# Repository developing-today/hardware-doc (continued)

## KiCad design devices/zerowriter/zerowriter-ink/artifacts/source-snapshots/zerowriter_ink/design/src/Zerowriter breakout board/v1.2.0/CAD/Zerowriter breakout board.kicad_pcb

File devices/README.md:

# Hardware devices

Each device record links to **every component it contains**; each [component record](../components/README.md) links back to the devices that use it, and to its [vendor sourcing guide](../vendors/README.md).

## Seeed Studio

- [Seeed Studio XIAO ESP32S3 Sense](seeed-studio/xiao-esp32s3-sense/README.md), SKU 113991115, retrieved 2026-08-24 — vendor guide: [Seeed Studio](../vendors/seeed-studio/README.md)

A 17.78 x 21.14 mm ESP32-S3R8 board with a detachable camera / PDM microphone / microSD daughterboard on a 30-pin Hirose board-to-board connector. Notable because Seeed publishes **KiCad sources under CC BY-SA 4.0**, which allowed the otherwise-undocumented [board-to-board connector pinout](seeed-studio/xiao-esp32s3-sense/pinouts-and-buses.md#2-the-j3-board-to-board-connector-sense-daughterboard-interface) to be reconstructed from the PCB netlist.

Three findings from that pass are worth knowing before buying one: the **user LED and the microSD chip-select are the same pin**; the **daughterboard consumes all four JTAG pins**, so hardware debugging is impossible with it attached; and the shipped **factory firmware contains hardcoded Wi-Fi credentials** and cannot connect to your network.

## Waveshare

- [Waveshare ESP32-S3-Knob-Touch-LCD-1.8](waveshare/esp32-s3-knob-touch-lcd-1.8/README.md), product ID 31623, retrieved 2026-08-21 — vendor guide: [Waveshare](../vendors/waveshare/README.md)
- [Waveshare ESP32-S3-ePaper-3.97](waveshare/esp32-s3-epaper-3.97/README.md), SKUs **33552 / 33810 / 33811**, **USD 34.99–47.99**, retrieved 2026-09-01 — the knowledge base's first Waveshare **e-paper** board (all others are LCD). Same SoC, memory, 3.97" 4-grey panel **and SSD1677 controller** as the [M5Stack PaperMono](m5stack/papermono/README.md); active area matches to 0.01 mm and DPI exactly. **It has no expansion header** — which refutes the "prefer a Waveshare board *with expansion*" advice it was written to support. Schematic, panel manual and vendor source retained; [pinouts](waveshare/esp32-s3-epaper-3.97/pinouts-and-buses.md) · [conflicts](waveshare/esp32-s3-epaper-3.97/gaps-and-conflicts.md)

**Waveshare's other ESP32 e-paper boards** — surveyed 2026-09-01, stub records, not researched in depth. Recorded so the population is known:

| Board | Price, 2026-09-01 | Why it is here |
|---|---|---|
| [e-Paper ESP32 Driver Board](waveshare/e-paper-esp32-driver-board/README.md) | USD 14.99 | Original ESP32; drives **23 documented raw panels** over a 24-pin FPC. The oldest and most widely deployed of the family |
| [ESP32-S3-ePaper-1.54](waveshare/esp32-s3-epaper-1.54/README.md) | USD 15.99–22.99 | 1.54" 200 × 200. **Has the 2 × 6 2.54 mm expansion header the 3.97" lacks** — 40 000 pixels instead of 384 000 |
| [ESP32-C6-ePaper-1.54](waveshare/esp32-c6-epaper-1.54/README.md) | USD 16.99–17.99 | Same, on **ESP32-C6 — Wi-Fi 6, Zigbee/Thread**, plus a TCA9554 I/O expander |
| [ESP32-S3-PhotoPainter](waveshare/esp32-s3-photopainter/README.md) | USD 82.99–83.99 | 7.3" Spectra 6 in a wood frame. **An appliance, not a development board** — and the `PhotoPainter` name covers four products, only one of which is ESP32 |

A sibling of this board, the **Guition JC3636K518**, is documented — as far as the evidence allows — in [clones-and-variants.md §5](../guides/markets/clones-and-variants.md#5-worked-example--waveshare-knob-board-and-guition-jc3636k518). It is not a separate device record here because we have not handled one.

### ESP32-P4 round-display boards

Retrieved 2026-08-24. Two variants of **one PCB**, differing only in the fitted round MIPI-DSI panel. Both use the [ESP32-P4](../components/espressif/esp32-p4/README.md) with an ESP32-C6-MINI-1 companion radio over SDIO — the same no-radio-on-the-P4 pattern as Espressif's own boards below.

| Board | Panel | Status | Notes |
|---|---|---|---|
| [ESP32-P4-WIFI6-Touch-LCD-3.4C](waveshare/esp32-p4-wifi6-touch-lcd-3.4c/README.md) | 3.4″ **800 × 800** | on sale, SKU **31523** | Crisper (~333 ppi) |
| [ESP32-P4-WIFI6-Touch-LCD-4C](waveshare/esp32-p4-wifi6-touch-lcd-4c/README.md) | 4″ **720 × 720** | on sale, SKU **31522** | Larger but coarser (~255 ppi) |
| [Shared XC platform record](waveshare/esp32-p4-wifi6-touch-lcd-xc-shared/README.md) | — | — | Schematic, demo archive, pin map, architecture |

`XC` is Waveshare's own family wildcard: both wikis link the **same** schematic and demo archive under an `ESP32-P4-WIFI6-Touch-LCD-XC` path, so those artifacts are stored once. The variants differ in exactly three things — resolution constants, the physical panel, and a single byte in the JD9365 init sequence.

Both are sold under **one listing** at $64.99–$74.99 via a *Version Options* selector — the URL says `3.4c` but serves both. Waveshare maintain an official Apache-2.0 repository, a published BSP component (`waveshare/esp32_p4_wifi6_touch_lcd_xc` 3.0.1) and factory firmware for both: see [official repo and community](waveshare/esp32-p4-wifi6-touch-lcd-3.4c/official-repo-and-community.md).

## Espressif — official ESP32-P4 development boards

Retrieved 2026-08-21. All five are built on the [ESP32-P4](../components/espressif/esp32-p4/README.md), which has **no radio**; each carries a companion Wi-Fi/Bluetooth module. The `P4X` prefix denotes a board fitted with ESP32-P4 chip revision **v3.1 or later** — it is **not** a different chip.

| Board | Status | Companion radio | Distinguishing feature | Sources |
|---|---|---|---|---|
| [ESP32-P4X-Function-EV-Board](espressif/esp32-p4x-function-ev-board/README.md) | current | ESP32-C6-MINI-1 (2.4 GHz Wi-Fi 6) | Flagship multimedia board: 7″ 1024×600 MIPI-DSI touch panel, MIPI-CSI camera, Ethernet, audio, USB HS host + device | [manifest](espressif/esp32-p4x-function-ev-board/sources.md) |
| [ESP32-P4X-C5-Function-EV-Board](espressif/esp32-p4x-c5-function-ev-board/README.md) | current | **ESP32-C5-MINI-1 (2.4 + 5 GHz Wi-Fi 6)** | Same design with **dual-band** Wi-Fi; **the only P4 board whose main-board schematic, PCB layout and dimensions Espressif publishes** | [manifest](espressif/esp32-p4x-c5-function-ev-board/sources.md) |
| [ESP32-P4X-EYE](espressif/esp32-p4x-eye/README.md) | current | ESP32-C6-MINI-1U (external antenna) | Enclosed hand-held **camera**: 2 MP MIPI-CSI, 1.54″ SPI LCD, rotary encoder, battery, on-device YOLOv11-nano demo | [manifest](espressif/esp32-p4x-eye/sources.md) |
| [ESP32-P4-Function-EV-Board](espressif/esp32-p4-function-ev-board/README.md) | **EOL** | ESP32-C6-MINI-1 | Predecessor of the P4X board; **retains the published schematic / PCB / dimensions / assembly set** | [manifest](espressif/esp32-p4-function-ev-board/sources.md) |
| [ESP32-P4-EYE](espressif/esp32-p4-eye/README.md) | **EOL** | ESP32-C6-MINI-1U | Predecessor of the P4X-EYE; **retains the published schematic and PCB layout** | [manifest](espressif/esp32-p4-eye/sources.md) |

⚠ **Both EOL user guides moved between 2026-08-21 and 2026-08-28** — Espressif dropped the `eol/`
path segment, the originally-cited URLs now return HTTP 404, and neither has an Internet Archive
capture. Current URLs and the full finding are in
[the EOL board's manifest §4](espressif/esp32-p4-function-ev-board/sources.md#4-retrieval-findings).

There is **no ESP32-P4 Korvo board.** The Korvo line is an audio/HMI family built on the ESP32-S3 (`ESP32-S3-Korvo-2`, `ESP32-S3-Korvo-2-LCD`) and the newer S3.1 (`ESP32-S31-Korvo-1`). See [ESP32-P4 §1](../components/espressif/esp32-p4/README.md#1-identity-and-variants) and the board records above.

Documents Espressif publishes once and links from several of these boards are stored in [`espressif/shared-artifacts/`](espressif/shared-artifacts/README.md) rather than duplicated into each board.

The companion-radio arrangement these five boards share — and how it contrasts with the ESP32-S3 + ESP32-U4WDH retrofit on the Waveshare knob board — is mapped in [ecosystem-and-product-lines.md §6](../guides/espressif/ecosystem-and-product-lines.md#6-the-companion-radio-pattern-p4--c6c5).

## Soldered Electronics

Retrieved 2026-08-24. Osijek, Croatia — makers of the **Inkplate** e-paper series. Vendor guide: [Soldered Electronics](../vendors/soldered-electronics/README.md).

| Board | Panel | Hardware rev | Arduino target | Sources |
|---|---|---|---|---|
| [Inkplate 5](soldered-electronics/inkplate-5/README.md) | 5.2″ **960 × 540** | V1.2.0 | `Inkplate5` | [manifest](soldered-electronics/inkplate-5/sources.md) |
| [Inkplate 5 Gen 2](soldered-electronics/inkplate-5-gen2/README.md) | 5.2″ **1280 × 720** | V1.1.0 | `Inkplate5V2` | [manifest](soldered-electronics/inkplate-5-gen2/sources.md) |

Both generations share **one full technical record** — [`inkplate-5/README.md`](soldered-electronics/inkplate-5/README.md) — because they differ in **exactly one component**, the panel. Everything else (ESP32-WROVER, TPS65186 PMIC, PCAL6416A expander, PCF85063A RTC) is common. The Gen 2 keeps its own page because Soldered publish its hardware design in a **separate upstream repository**.

Worth knowing before integrating one: Soldered ship **CE and UKCA compliance documents and multilingual safety sheets inside the public hardware repository**, which is unusually thorough for an open-hardware vendor. Hardware is **TAPR OHL**; the Arduino library is **LGPL-3.0**.

## ZeroWriter

Open-source e-paper typewriters by Adam Wilk. Vendor guide: [Zerowriter](../vendors/zerowriter/README.md).

| Device | Status | Platform | Retrieved |
|---|---|---|---|
| [ZeroWriter Ink](zerowriter/zerowriter-ink/README.md) | shipping since Jan 2026; Crowd Supply, funded 2024-10-17, $285 | Respun [Inkplate 5 Gen 2](soldered-electronics/inkplate-5-gen2/README.md) + a second ESP32 for the keyboard | 2026-08-24 |
| [Zerowriter Fold](zerowriter/zerowriter-fold/README.md) | **unshipped** — Kickstarter live at snapshot, ~$239 First Wave / ~$329 retail, ships late 2026 | Claimed **in-house** hardware; 6″ **frontlit** e-ink, folding laptop-style case, hot-swap Choc keyboard | 2026-08-24 |

**ZeroWriter Ink** was built **in collaboration with Soldered Electronics**. The headline finding is that the device contains **two ESP32s** — an ESP32-WROVER on the display board and an ESP32-WROOM-32U-N4 on the keyboard PCB — which is stated nowhere in the campaign material and was recovered only from the project's own KiCad BOMs.

Its main board is a **respin of the [Inkplate 5 Gen 2](soldered-electronics/inkplate-5-gen2/README.md)**, not the stock product: 8 parts added, 14 removed, 20 values changed, including a swap from a linear to a switch-mode charger. Firmware written against the Inkplate Arduino library should run, but **power, charging, USB and SD paths differ** — see [the BOM comparison](zerowriter/zerowriter-ink/README.md).

Its Raspberry-Pi predecessor, **ZeroWriter 1**, silently patched two files in Waveshare's vendored e-paper driver library; both changes are analysed in [zerowriter1-epaper-driver-notes.md](zerowriter/zerowriter-ink/zerowriter1-epaper-driver-notes.md).

**Zerowriter Fold** is documented **from vendor marketing material only** — the Kickstarter campaign page bot-blocks every user agent tried and was never read. No design files, teardown, review or unit exists. Treat every figure as a vendor claim about an unshipped product; the record's [source manifest](zerowriter/zerowriter-fold/sources.md) states exactly what that evidence can and cannot support. The consequential claim is that the Fold uses **in-house hardware** rather than an Inkplate — if accurate, none of the Inkplate research transfers to it.

## M5Stack

Retrieved **2026-09-01**. Two SKUs of **one board**, launched together on 2026-08-21 and both out of stock nine minutes later.

| Board | SKU | Price | Distinguishing feature | Sources |
|---|---|---|---|---|
| [PaperMono](m5stack/papermono/README.md) | **C153** · FCC **`2AN3WM5PAPERMONO`** | USD 65.00 | Grey case, **NFC (ST25R3916) + LoRa (Stamp LoRa-1262)** | [**certification**](m5stack/papermono/certification.md) · [sources](m5stack/papermono/sources.md) · [research log](m5stack/papermono/research-log.md) · [commands](m5stack/papermono/commands.md) |
| [PaperMono-Lite](m5stack/papermono-lite/README.md) | **C153-Lite** / `C153-LITE` | USD 55.00 | White case, **no NFC, no LoRa**; 72.4 g vs 74.7 g. Everything else identical, battery included | shares the PaperMono's manifests |

> **Certification, 2026-09-20.** The PaperMono record previously said in seven
> places that no certification of any kind existed for this board. **It is
> certified** — FCC ID **`2AN3WM5PAPERMONO`**, two grants issued 2026-08-12 — and
> M5Stack simply publishes nothing about it. The filing's eleven exhibits have
> been mined into [`certification.md`](m5stack/papermono/certification.md):
> certified bands and conducted power per mode, the antenna's measured gain
> (**−5 dBi** at 910 MHz, 15.9 % efficient), SAR at **0 mm on all six faces**,
> and **the only public PCB photographs of this board**. Two things a builder
> needs: **US LoRa is 903.0–914.9 MHz only**, and **Wi-Fi and BLE cannot transmit
> simultaneously**. M5Stack also filed its **full architecture diagram as the FCC
> label**, which is a second primary source for the pin map.

A 3.97″ 480 × 800 frontlit touch e-paper handheld on an ESP32-S3R8. Best understood as **a battery-first low-power platform that happens to have a display**, not an e-paper board that happens to have a battery: it has five hardware power states and can wake on RTC alarm, motion, touch or keys **with the application processor unpowered**. The full record: [`papermono/`](m5stack/papermono/README.md), with [pinouts and buses](m5stack/papermono/pinouts-and-buses.md), [power architecture](m5stack/papermono/power-architecture.md) and [gaps and conflicts](m5stack/papermono/gaps-and-conflicts.md).

Four things to know before buying or building for one:

- **There is no expansion connector at all** — no Grove, no M-Bus. Every GPIO is committed; the only way in is the shared I²C bus. This is unusual for an M5Stack core and is the single biggest constraint.
- **Two auxiliary microcontrollers sit between the application processor and most of the board.** Panel power and reset, touch power and reset, microSD power and detect, microphone power, NFC enable, LoRa reset, two of three LED colours and the charger's bus gate are all behind the **M5IOE1** expander; reset, boot mode, rail enables and every wake source are behind the **M5PM1** power manager. Neither is optional, and both are the *same* Puya PY32L020F15U6 die running different M5Stack firmware.
- **`PYG3` denotes two different pins**, one on each of those chips — the frontlight PWM and the e-paper rail enable. Getting it wrong silently kills the display. [The whole hazard, and how it was resolved from the schematic](m5stack/papermono/pin-naming-and-the-pyg-ambiguity.md).
- **Do not read PaperMono as a successor to the M5PaperS3.** Against the PaperS3 it has ~35 % fewer pixels, 4 grey levels instead of 16, a smaller battery and no expansion port, while adding a frontlight, NFC, LoRa and the power architecture. A repositioning, not an upgrade.

⚠ **Nothing in either record was verified on physical hardware.** Every behavioural claim is `inferred`, `reported-working` or read from vendor source. The board sold out within minutes of launch and had not restocked eleven days later, so no unit could be obtained — and for the same reason there were, at the snapshot date, **zero written reviews and one hands-on video** anywhere. The real independent evidence is four third-party GitHub projects, two with credible hardware validation.

M5Stack publishes a complete schematic and datasheets for both of its custom chips, which is better hardware disclosure than most comparable vendors — but **no C153 directory exists in `m5stack/M5_Hardware`**, so there is no machine-readable netlist and the pin map was recovered by parsing invisible Altium marker text out of the published PDF. Method and limitations: [`commands.md`](m5stack/papermono/commands.md#altium-pdf-tooling).

### DinMeter — *added 2026-09-04*

A 1/32-DIN panel instrument built on a Stamp module: orange rotary encoder, 1.14" display, buzzer and a **6–36 V DC input**, in a DIN 43700 cutout. M5Stack publishes a **byte-identical** schematic and STL for both revisions, so the v1.1 record is scoped to the module substitution that is the entire content of the revision.

| Device | SKU | Record | Notes |
|---|---|---|---|
| **DinMeter** | `K134` | [`m5stack/dinmeter`](m5stack/dinmeter/README.md) | 1/32-DIN panel instrument: orange rotary encoder, 1.14" ST7789V2 135×240, BM8563 RTC, buzzer, **6–36 V DC input**, Li-ion charger + latch, PORT.A/B. Stamp-S3 core module. **`[EOL]` at the vendor, 2026-09-04** |
| **DinMeter v1.1** | `K134-V11` | [`m5stack/dinmeter-v1.1`](m5stack/dinmeter-v1.1/README.md) | Same carrier with a **Stamp-S3A** module and an ST7789P3 display. Scoped revision record — M5Stack publishes a **byte-identical** schematic and STL for both. Includes [`stamp-s3-to-s3a-delta.md`](m5stack/dinmeter-v1.1/stamp-s3-to-s3a-delta.md), the full schematic-derived module delta |

### Cardputer family — *added 2026-09-04*

Card-sized computers with a 56-key QWERTY keyboard over a 1.14″ 240×135 display. Five records; the ADV is the full-depth one. Note that **the v1.0 and v1.1 share one published schematic file byte-for-byte** (SHA-256 `6016c1fe…`), so the revision is a module substitution — Stamp-S3 → Stamp-S3A — with an undocumented or unchanged mainboard, and the document alone cannot say which.

| Device | Manufacturer | SKU | SoC | Notes |
|---|---|---|---|---|
| [Cardputer ADV](m5stack/cardputer-adv/README.md) | M5Stack | `K132-Adv` | ESP32-S3FN8 | Card-sized computer, 56-key TCA8418 keyboard, ES8311 audio, BMI270, 14-pin CAP expansion header. **Full-depth record.** |
| [Cardputer v1.1](m5stack/cardputer-v1.1/README.md) | M5Stack | `K132-V11` | ESP32-S3FN8 | Stamp-S3A refresh of the original; 74HC138 keyboard. **`[EOL]` at 2026-09-04.** |
| [Cardputer v1.0](m5stack/cardputer-v1.0/README.md) | M5Stack | `K132` | ESP32-S3FN8 | The original; StampS3 module. Shares a published schematic file with v1.1. |
| [Cardputer Mesh Kit](m5stack/cardputer-mesh-kit/README.md) | M5Stack | `K152` | ESP32-S3FN8 | Cardputer ADV + Cap LoRa-1262 bundle; officially licensed Meshtastic device. |
| [CardputerZero](m5stack/cardputer-zero/README.md) | M5Stack | `C154` / `C155` | **Raspberry Pi CM0** | Linux handheld in the Cardputer form factor. Vendor marks it *work in progress*. |

⚠ **The Cardputer ADV and the CardputerZero are not comparable devices** despite sharing a name, a form factor, a keypad scanner and an expansion connector: one is a microcontroller, the other a Linux computer, and their EXT headers are **not pin-compatible** — the Zero's left column is USB/GPIO/SPI0 and its UART pair is reversed relative to the ADV's.

### Cardputer expansions — LoRa, sub-GHz and NFC — *added 2026-09-04*

Nine records covering M5Stack's radio expansions for the Cardputer line, from the Grove-attached E220 units of 2023 to the **Cap CC1101 & NFC** released 2026-08-28. Entry point: [`m5stack/cap-lora-1262/`](m5stack/cap-lora-1262/README.md); the two portability-focused guides are [`features/lora.md`](m5stack/cap-lora-1262/features/lora.md) and [`features/nfc.md`](m5stack/cap-cc1101/features/nfc.md), both written for someone adding these capabilities to *other* firmware.

| Device | Notes | Depth |
|---|---|---|
| [M5Stack Cap LoRa-1262 (U214)](m5stack/cap-lora-1262/README.md) | Cardputer-Adv expansion — SX1262 LoRa + ATGM336H-6N GNSS, 868–923 MHz, Meshtastic-supported upstream | full |
| [M5Stack Cap CC1101 & NFC (U219)](m5stack/cap-cc1101/README.md) | Cardputer-Adv expansion — CC1101 sub-GHz (315/433/868/915 MHz, dual SP3T switched) + ST25R3916 NFC over SPI | full |
| [M5Stack Cap LoRa868 (U201)](m5stack/cap-lora868/README.md) | The **first** Cardputer-Adv LoRa expansion, 2025-09-05, now EOL — predecessor of the Cap LoRa-1262 | medium |
| [M5Stack Cardputer Mesh Kit (K152)](m5stack/cardputer-mesh-kit/README.md) | Bundle: Cardputer-Adv + Cap LoRa-1262, pre-flashed Meshtastic, the only Meshtastic-registration-eligible configuration | medium |
| [M5Stack LoRa Unit (E220)](m5stack/unit-lora-e220/README.md) | Grove/UART LLCC68 modem — attaches to *any* Cardputer, but **not** a Meshtastic path | light |
| [M5Stack LoRaWAN Unit (STM32WLE5)](m5stack/unit-lorawan-stm32wle5/README.md) | Grove/UART LoRaWAN modem, **region per SKU**, RAK3172 module | light |
| [M5Stack Unit C6L (U202)](m5stack/unit-c6l/README.md) | Self-contained ESP32-C6 + SX1262 Meshtastic node on a Grove cable — the route for an **original** Cardputer | light |
| [M5Stack Stamp C6LoRa (S012)](m5stack/stamp-c6lora/README.md) | Solder-down ESP32-C6 + SX1262 SMD module — **not** a Cardputer expansion | light |

⚠ **Initialising the Cap LoRa-1262 requires one non-obvious step**: M5Stack states that the RF antenna switch must be enabled by setting **`P0` of the Cap's PI4IOE I/O expander HIGH**, over the host's *internal* I²C bus. Omit it and the radio transmits into a disconnected antenna.

## Xteink (阅星瞳 / 星瞳 "Star Pupil")

Shenzhen maker of low-cost pocket e-ink readers, and the hardware target of the
CrossPoint Reader / FreeInk firmware ecosystem. **Six products**, four of them
ESP32-based. See the [family index](xteink/README.md).

| Device | SoC | Panel | Price (2026-09-04) | Record |
|---|---|---|---|---|
| [X4 Pro](xteink/x4-pro/README.md) | ESP32-S3, 8 MB PSRAM | 4.26″ 800×480, GT911 touch, warm/cool frontlight | **$99** | deep |
| [X4](xteink/x4/README.md) | ESP32-C3 | 4.26″ 800×480 | **delisted** | deep |
| [X3](xteink/x3/README.md) | ESP32-C3 | 3.7″ 792×528, ~257 PPI, IMU + NFC | **$69** | deep |
| [X4 Classic](xteink/x4-classic/README.md) | ESP32-S3, 8 MB PSRAM | 4.26″ 800×480, 7 buttons, IMU | not listed | medium |
| [S4](xteink/s4/README.md) | **Android 11** | not established | ¥339 (China) | stub |
| [Nano / Tong Card 瞳卡](xteink/nano/README.md) | **none — passive NFC-powered** | four-colour e-paper card | not captured | stub |

**Note the naming trap:** the X4 Pro is *not* an enhanced X4. They share a screen
size and a brand; different SoC architecture, flash layout, input hardware and
charging connector. Firmware for one will not run on the other.

Three axes of variation are **invisible from outside** and none is externally marked: the **panel controller** (the X3 ships a UC8253 *or* a UC8279d; the X4 family an SSD1677 *or* UC8179 *or* UC8279 — firmware probes the display bus at boot, **except on the X4 Classic, which has no MISO and must trust an NVS byte the factory wrote once**); the **power latch** (at least one X4 revision does not self-latch); and the **USB-lock state**, which owners find **does not correlate with sales channel**.

### Round-two corrections — *2026-09-11*

⚠ **Two rows in the table above are now wrong, and one device is missing from it.** Per this
repository's append-only rule the stale rows are **left exactly as written**; the corrections are
here. The family index [`xteink/README.md`](xteink/README.md) carries the full corrected table.

**1. The X4 Classic launched on 2026-09-06, and it replaced the X4.**
The row above says *"not listed"*. It is listed, and the X4 row's price is the one that is now
historical:

| Device | Marketed as | Listed | Price | Status 2026-09-11 |
|---|---|---|---|---|
| [X4 Classic](xteink/x4-classic/README.md) | **"XTEINK X4 Classic (X4 V2)"** | **2026-09-06** | **USD 79** bare / 95 with base | on sale, in stock |
| [X4](xteink/x4/README.md) | — | — | last observed ~USD 69 | **withdrawn — the product record *and all four of its dedicated accessories* are gone from the catalogue** |

**The vendor's own store title asserts the succession**: the Classic *is* the second version of
the X4. The FCC record agrees — `2BTR9-XTEINKX4` granted 2026-01-05, then `2BTR9-X4C` granted
2026-07-20. On 2026-09-04 the X4's four accessories were still listed but sold out; a week later
the product records themselves had been removed. **That is a completed withdrawal, not a
stockout.**

**2. There is a sixth device, and the vendor has never mentioned it.**

| Device | SoC | Panel | Price | Record |
|---|---|---|---|---|
| [X4 Light](xteink/x4-light/README.md) | **unknown** | **unknown** | **never listed** | certification-only |

**FCC `2BTR9-X4L`, granted 2026-08-13.** No announcement, no store listing, no price, no review,
no community mention. It was found by **enumerating Xteink's FCC grantee code `2BTR9`**, not by
searching for a product name — a vendor's grantee index lists every device it has certified for
the US, including ones it has never announced. Its internal photographs unlock **2027-02-09**;
its external photographs are already public and held in the record. ⚠ **"Light" is a marketing
word and the filing does not define it** — do not infer a specification or a price slot from the
name.

That makes the table above **seven entries**, not six. Four are confirmed ESP32-based; the X4
Light's SoC is **unknown**, and the Nano is a passive NFC card rather than a reader.

**3. ⚠ The certification finding for this family is reversed.** Records in this tree stated that
no FCC or CE filing existed for any Xteink device. **Refuted.** Xteink holds **five granted
Original Equipment authorisations** under grantee code `2BTR9` — X3, X4, X4 Pro, X4 Classic and
X4 Light. The original finding confused *"no mark visible in a product photo"* with *"no grant"*.
Per-device detail and the positive/negative controls that make it evidence:
`xteink/<record>/certification-and-compliance.md`. Corrections are appended beneath every stale
claim and listed in
[`research/passes/index-merge/corrections-requiring-review.md`](../research/passes/index-merge/corrections-requiring-review.md).

One consequence worth surfacing at index level: the `2BTR9-XTEINKX4` filing's **Internal Photos
were never withheld**, which makes them the **first public teardown of the Xteink X4** —
[`xteink/x4/artifacts/certification/`](xteink/x4/artifacts/certification/README.md). The X3's are
public too; the X4 Pro's unlock **2026-12-12**. Schematics are withheld **permanently** on all
five filings, so the FCC is not a route to an Xteink schematic.

## LilyGO (Shenzhen Xin Yuan Electronic Technology; also trades as TTGO)

Vendor guide: [LilyGO / TTGO](../vendors/lilygo/README.md). The **T-Display-S3 family** is a *name*, not a platform: eleven boards, eight display
controllers and four different chargers ship under it. Start at the shared platform record.

| Device | Identity | Depth |
|---|---|---|
| [T-Display-S3 family — shared platform](lilygo/t-display-s3-shared/README.md) | family hub: enumeration evidence, shared artifacts, family-wide traps, [board-revision drift](lilygo/t-display-s3-shared/board-revision-drift.md) | — |
| [T-Display-S3](lilygo/t-display-s3/README.md) | ESP32-S3R8 + 1.9″ 170×320 ST7789V on an **8-bit Intel-8080 parallel** bus. USD 9.04 | **full** |
| [T-Display-S3 Touch](lilygo/t-display-s3-touch/README.md) | same PCB; panel swapped for one with a bonded CST816S → later CST328 | medium |
| [T-Display-S3 AMOLED](lilygo/t-display-s3-amoled/README.md) | 1.91″ 240×536 RM67162 on QSPI; **V1.0 and V2.0 sold concurrently** | full-ish |
| [T-Display-S3 AMOLED Plus](lilygo/t-display-s3-amoled-plus/README.md) | same panel, BQ25896 PMIC + PCF85063ATL RTC + microSD | medium |
| [T-Display-S3 AMOLED 1.64″](lilygo/t-display-s3-amoled-1-64/README.md) | 280×456 CO5300/ICNA3311 + FT3168 + SY6970 | medium |
| [T-Display-S3 AMOLED 1.43″/1.75″](lilygo/t-display-s3-amoled-1-43-1-75/README.md) | round 466×466; **two display and two touch controllers behind one product page** | medium |
| [T4-S3](lilygo/t4-s3/README.md) | the "2.41″ AMOLED": 450×600 RM690B0 + CST226SE. Sold as *T4-S3*, not T-Display-S3 | medium |
| [T-Display AMOLED Lite](lilygo/t-display-amoled-lite/README.md) | 1.47″ 194×368 SH8501B behind a **1.8 V level shifter**; AXP2101 PMU | medium |
| [T-Display-S3 Long](lilygo/t-display-s3-long/README.md) | 3.4″ 180×640 bar; **AXS15231B drives display *and* touch from one die** | full-ish |
| [T-Display-S3 Pro](lilygo/t-display-s3-pro/README.md) | 2.33″ 222×480 ST7796 on plain SPI, camera, microSD, 3 buttons, SY6970 | full-ish |
| [T-Display-S3 Pro MVSRBoard](lilygo/t-display-s3-pro-mvsrboard/README.md) | audio/RTC/haptic backplate for the Pro | stub |
| [T-Display (TTGO, ESP32)](lilygo/t-display-ttgo/README.md) | the ancestor. 1.14″ 135×240 SPI. **The only one WLED supports** | lineage stub |
| [T-QT](lilygo/t-qt/README.md) | thumbnail-sized 128×128 cousin | lineage stub |
| [T-Dongle-S3](lilygo/t-dongle-s3/README.md) | USB-A dongle, 0.96″ ST7735, on-board microSD | lineage stub |
| [T-Display K230 / Kit](lilygo/t-display-k230/README.md) | **the repository's first RISC-V device** — see below | full |

### T-Display K230 — *added 2026-09-04*

- [`lilygo/t-display-k230`](lilygo/t-display-k230/README.md) — **T-Display K230** (SKU `K256`/`-A`/`-B`/`-C`) and **T-Display K230 Kit** (`K256-03`, `K277`, `K256-04`, `K256-04-A`). A 4.1″ AMOLED handheld running **Linux on a 64-bit RISC-V** Kendryte K230, with LoRa, a 2 MP MIPI camera, USB Ethernet, a 40-pin header, and an optional QWERTY keyboard base carrying an nRF9151 LTE-M/GNSS modem. **The repository's first RISC-V device.**

⚠ **LilyGO stock codes collide with chip names.** `K230` is a LilyGO SKU for the transparent-case variant of the **T-Embed CC1101**, an ESP32-S3 board with no Kendryte silicon in it. The Kendryte K230 board's SKUs are `K256*` and `K277`. **Never infer silicon from a LilyGO SKU** — and see the [vendor guide](../vendors/lilygo/README.md) for why the wiki must be verified against the board's GitHub repository.

---

## Nicolai Electronics

- [Nicolai Electronics Tanmatsu](nicolai-electronics/tanmatsu/README.md), retrieved 2026-08-24, hardware repo commit `640805dd` — "the terminal for hackers": an **ESP32-P4** handheld with a QWERTY keyboard, LoRa, a MIPI-DSI display and a 36-pin expansion port, derived from the Dutch hacker-camp badge lineage ([Badge.team](https://badge.team), MCH2022 / WHY2025) but sold as a product.

Notable for **openness rather than volume**: the full KiCad design is published under **CERN-OHL-P** and the firmware under **MIT**, with a git-maintained Sphinx documentation site. The limiting factor on information is that the device is new and low-volume, and the detail is spread across ~10 repositories.

> *Indexed 2026-09-07.* This record was written in the 2026-08-24 pass but was never linked from this index — an orphan found by the cross-link audit at the end of the 2026-09-04/07 sweep. The entry above is a discoverability fix written from the record's own opening section; **the record itself was not reviewed or modified**, and it remains the authority on its own contents.

---

## Flipper Devices

- [Flipper Devices Flipper Zero](flipper-devices/flipper-zero/README.md) — ⚠ **artifact-preservation stub, not a researched device record.** *Added 2026-09-20.*

Created solely to give six **Flipper Devices Inc.** schematic sheets (iButton, NFC, Power, Power and vibro, RFID, Sub-1 GHz CC1101) and seven teardown photographs a correctly-classified home. They were vendored as prior art into [`badgeteam/konsool-zero`](nicolai-electronics/tanmatsu/expansion-boards.md) — a Tanmatsu add-on — and a SHA-256 sweep confirmed they existed in exactly one place, inside a scratch clone.

**No product, pricing, firmware, community or component research has been done.** The sections a full device record requires are *absent, not empty*. What the sheets were mined for is narrow and stated in the record: they establish that konsool-zero copied the Flipper's sub-GHz and 125 kHz analog chains almost part-for-part, changing only the CC1101 reference (26 MHz crystal → 27 MHz oscillator) and the MCU (STM32WB55 → CH32V003F4U6) — which is also how a fabricated "STM32WB55CC on konsool-zero" claim got into this repository and was later refuted.

If you research the Flipper Zero properly, start from those artifacts and replace the stub.

---

## Two new per-record file types — *added 2026-09-11*

Round two of the 2026-09-04 sweep added two kinds of page to device records across the tree.
Neither is listed per-device above; both are worth knowing exist.

| File | What it is | Where |
|---|---|---|
| `certification-and-compliance.md` | Regulatory grants by jurisdiction — FCC ID, grant date, frequencies, test firm, withheld exhibits and embargo dates — **each carrying the positive and negative controls that make an absence finding mean anything**. Method: [`guides/research/finding-certification-records.md`](../guides/research/finding-certification-records.md) | **32 records**: M5Stack, LilyGO and all five Xteink |
| `schematic-netlist.md` | A net list **recovered from the vendor's schematic PDF**, not from EDA sources — connector pinouts, per-net membership and the unrouted or mislabelled nets the trace exposed. Method: [`guides/reverse-engineering/tracing-nets-from-schematic-pdfs.md`](../guides/reverse-engineering/tracing-nets-from-schematic-pdfs.md) | [`lilygo/t-display-s3-shared`](lilygo/t-display-s3-shared/schematic-netlist.md) · [`m5stack/cardputer-adv`](m5stack/cardputer-adv/schematic-netlist.md) · [`m5stack/dinmeter`](m5stack/dinmeter/schematic-netlist.md) · [`m5stack/cap-lora-1262`](m5stack/cap-lora-1262/schematic-netlist.md) · [`m5stack/cap-cc1101`](m5stack/cap-cc1101/schematic-netlist.md) |

Two of those boards also gained a `driver-vs-document-audit.md` — the vendor driver read
side-by-side against the schematic and the datasheet:
[`cardputer-adv`](m5stack/cardputer-adv/driver-vs-document-audit.md) (`M5Cardputer` @ `f1392858`)
and [`dinmeter`](m5stack/dinmeter/driver-vs-document-audit.md) (`M5DinMeter` @ `8ccbad7`).

**Why the tracing worked, and when it will not.** Altium exports embed invisible `CO` / `PI` /
`NL` marker tokens at item coordinates — component outlines, pins and net labels — so a net can
be reconstructed by geometry from the PDF text layer alone. **291 schematic PDFs in this
repository were assessed**; the per-file verdict is in
[`guides/reverse-engineering/schematic-pdf-traceability-census.md`](../guides/reverse-engineering/schematic-pdf-traceability-census.md).
Two traps that census found, both worth checking before concluding a design is undocumented:

- ⚠ **KiCad and EAGLE exports frequently outline their text to vector paths.** `pdftotext` then
  yields **zero words** and the file is permanently untraceable. For
  [`zerowriter/zerowriter-ink`](zerowriter/zerowriter-ink/README.md) and
  [`seeed-studio/xiao-esp32s3-sense`](seeed-studio/xiao-esp32s3-sense/README.md) **a second,
  usable export of the same design sits in the same directory** — prefer the `Eeschema` copies.
- ⚠ **Non-Altium exports carry no `CO`/`PI`/`NL` tokens**, so every binding must be geometric.
  That applies to the Espressif ESP32-P4 board schematics, which are otherwise traceable.

The richest untraced sheet in the repository is the **M5Stack PaperMono**'s
`PaperMono_SCH_V0.6.2` — 6 pages, 144 net-label tokens, fully traceable, and **not traced**,
because that record was owned by another session throughout both rounds.

---

## Related

- [Components](../components/README.md) — the parts these boards are built from
- [Vendor sourcing guides](../vendors/README.md) — [Espressif](../vendors/espressif/README.md) · [Waveshare](../vendors/waveshare/README.md)
- [Espressif ecosystem map](../guides/espressif/ecosystem-and-product-lines.md) · [Marketplace comparison](../guides/markets/vendor-comparison.md) · [Clones and variants](../guides/markets/clones-and-variants.md)

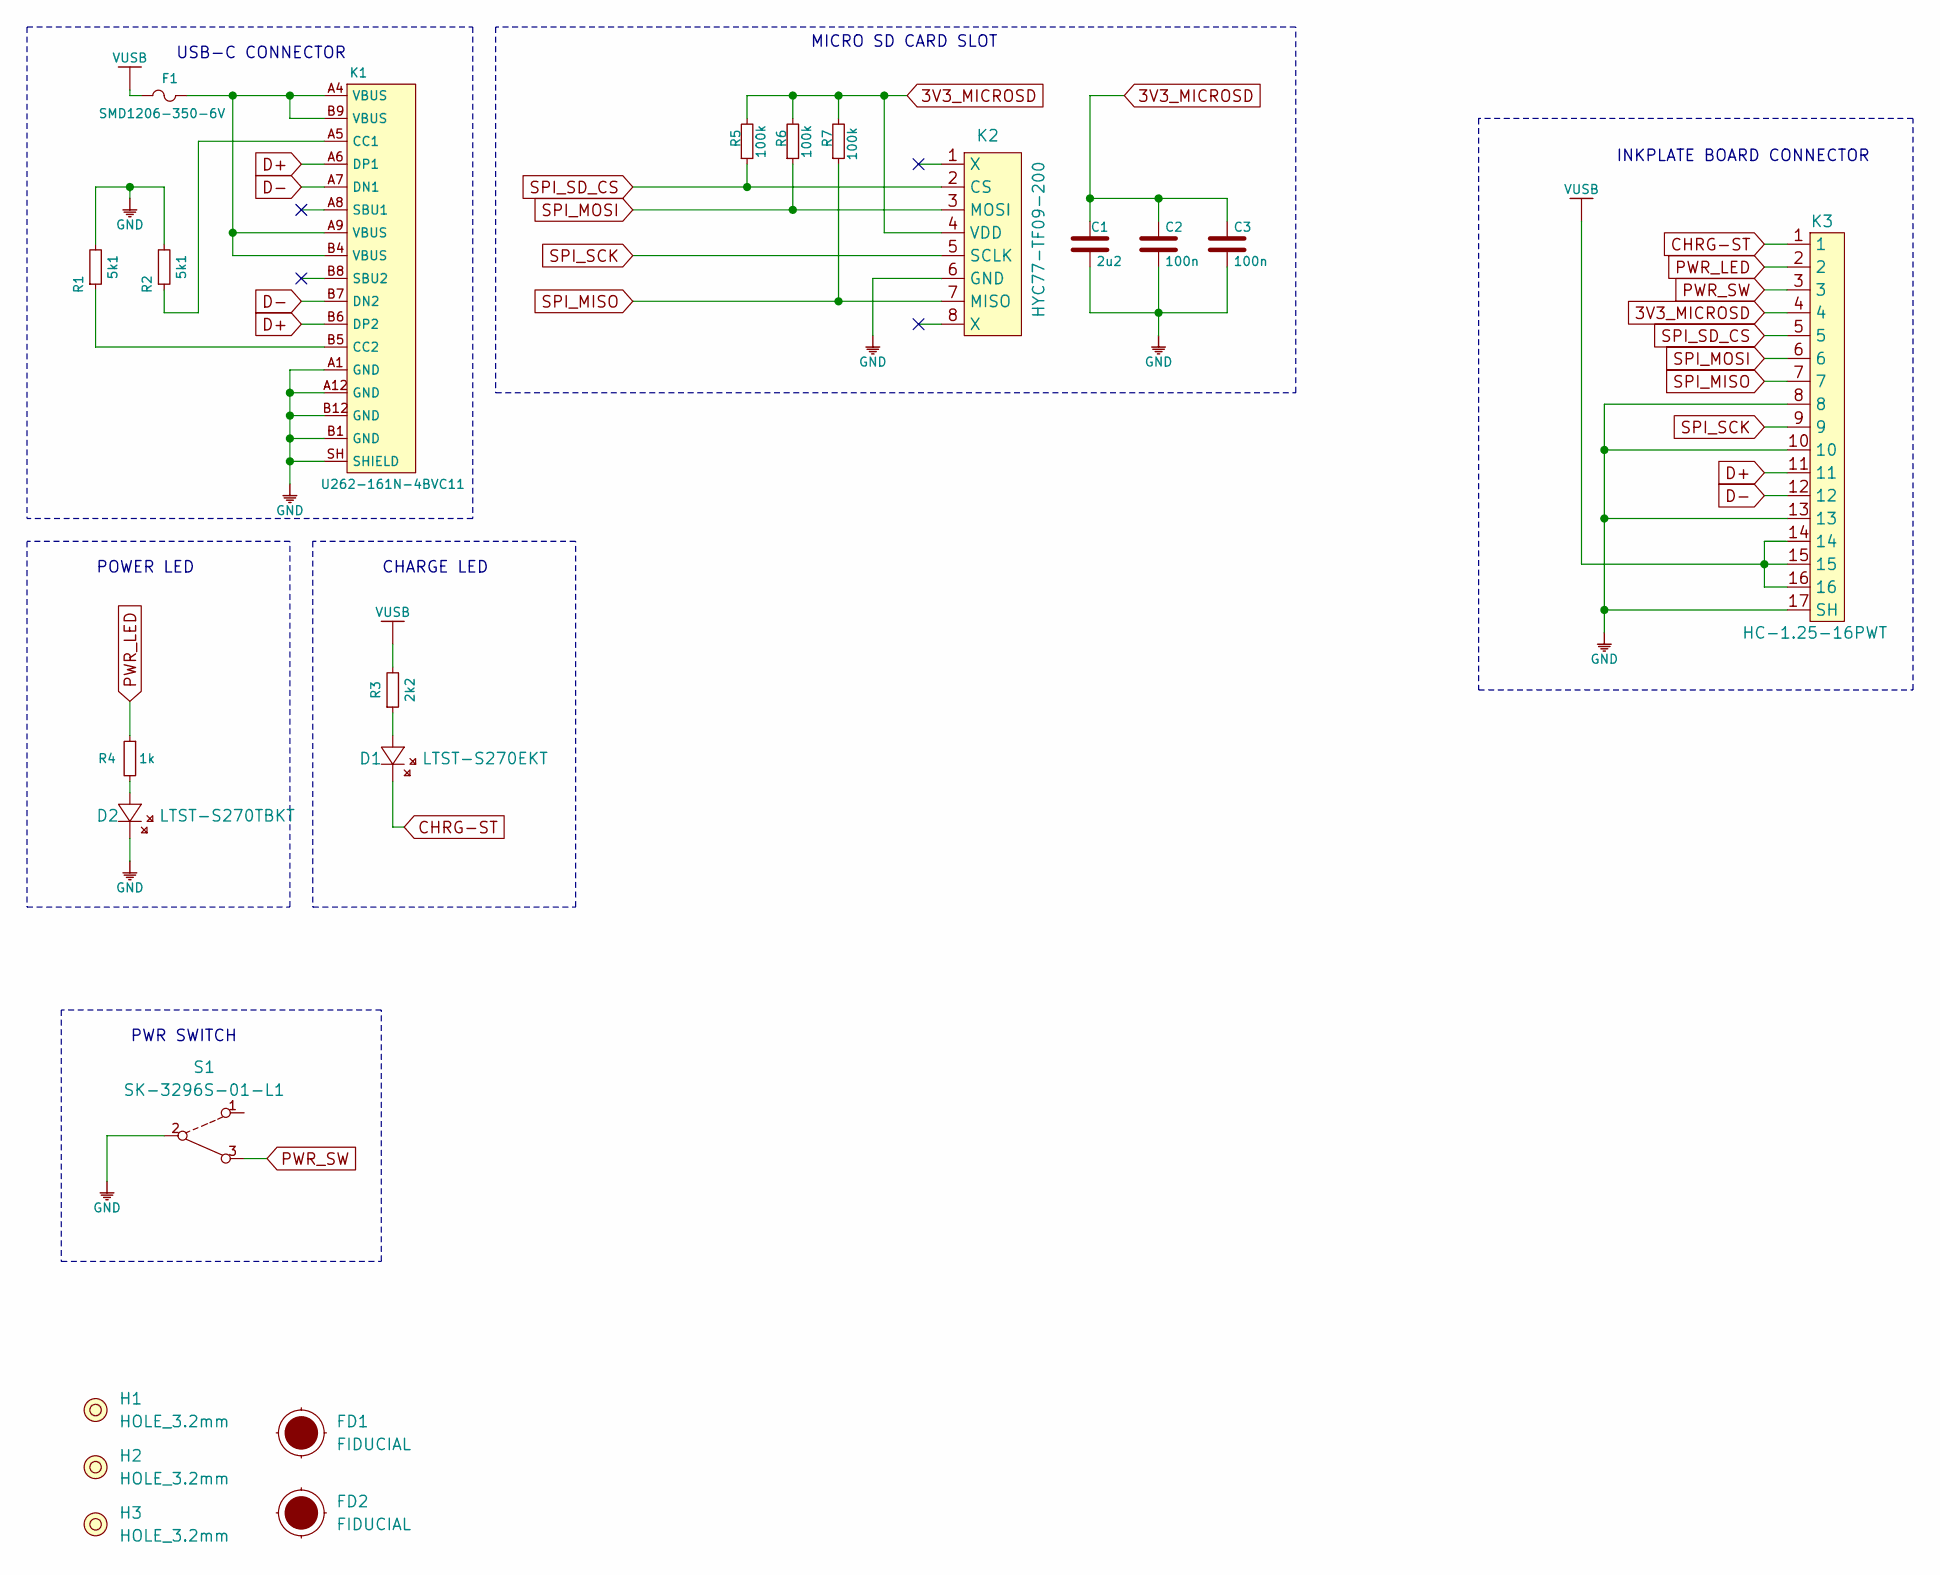
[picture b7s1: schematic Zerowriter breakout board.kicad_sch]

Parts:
C1: 2u2; 0603C
C2, C3: 100n; 0603C
D1: LTST-S270EKT; LTST-S270GKT
D2: LTST-S270TBKT; LTST-S270GKT
F1: SMD1206-350-6V; 1206FUSE
FD1, FD2: FIDUCIAL
H1, H2, H3: HOLE_3.2mm
K1: U262-161N-4BVC11
K2: HYC77-TF09-200
K3: HC-1.25-16PWT
R1, R2: 5k1; 0603R
R3: 2k2; 0603R
R4: 1k; 0603R
R5, R6, R7: 100k; 0603R
S1: SK-3296S-01-L1

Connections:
3V3_MICROSD: C1.2, C2.2, C3.2, K2.4 (VDD), K3.4, R5.2, R6.2, R7.2
CHRG-ST: D1.2 (K), K3.1
D+: K1.A6 (DP1), K1.B6 (DP2), K3.11
D-: K1.A7 (DN1), K1.B7 (DN2), K3.12
GND: C1.1, C2.1, C3.1, D2.2 (K), K1.A1 (GND), K1.A12 (GND), K1.B1 (GND), K1.B12 (GND), K1.SH (SHIELD), K2.6 (GND), K3.8, K3.10, K3.13, K3.17 (SH), R1.2, R2.2, S1.2
unnamed: D1.1 (A), R3.1
unnamed: D2.1 (A), R4.2
unnamed: F1.2, K1.A4 (VBUS), K1.A9 (VBUS), K1.B4 (VBUS), K1.B9 (VBUS)
unnamed: K1.A5 (CC1), R2.1
unnamed: K1.B5 (CC2), R1.1
PWR_LED: K3.2, R4.1
PWR_SW: K3.3, S1.3
SPI_MISO: K2.7 (MISO), K3.7, R7.1
SPI_MOSI: K2.3 (MOSI), K3.6, R6.1
SPI_SCK: K2.5 (SCLK), K3.9
SPI_SD_CS: K2.2 (CS), K3.5, R5.1
VUSB: F1.1, K3.14, K3.15, K3.16, R3.2

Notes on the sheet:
POWER LED
USB-C CONNECTOR
INKPLATE BOARD CONNECTOR
MICRO SD CARD SLOT
PWR SWITCH
CHARGE LED

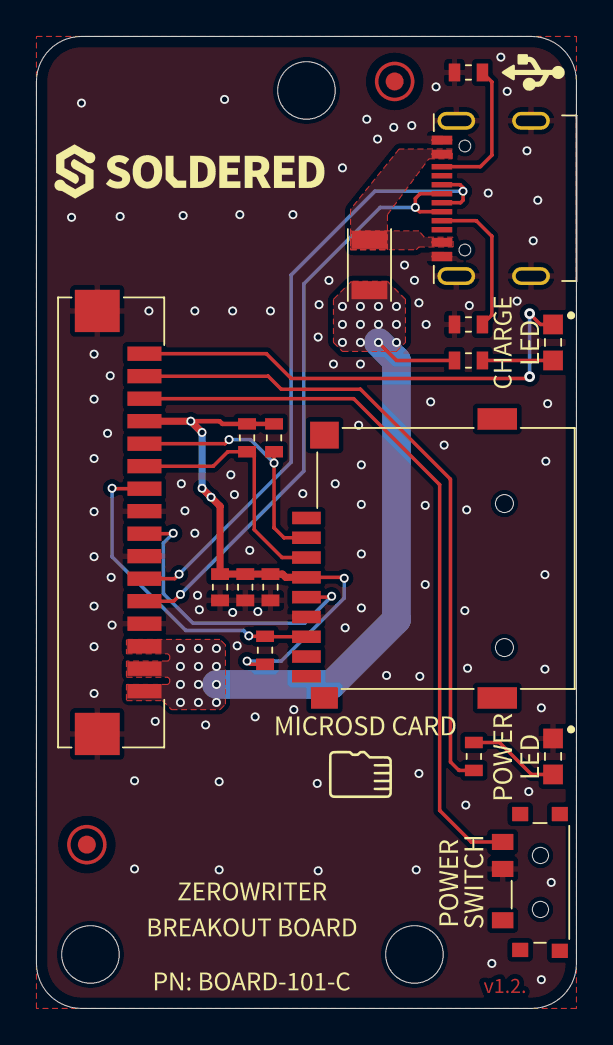
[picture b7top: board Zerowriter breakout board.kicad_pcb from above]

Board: 2 copper layers, 30.0 x 54.0 mm, 32 parts (0 on the bottom side), 17 nets.

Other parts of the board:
kibuzzard-63F8A516: G***; kibuzzard-63F8A516
kibuzzard-63F896F5: G***; kibuzzard-63F896F5
kibuzzard-63F8971E, kibuzzard-63F8971E#2: G***; kibuzzard-63F8971E
kibuzzard-63F89702: G***; kibuzzard-63F89702
kibuzzard-63F89711: G***; kibuzzard-63F89711
kibuzzard-672A36B8: G***; kibuzzard-672A36B8
kibuzzard-672A3648: G***; kibuzzard-672A3648
kibuzzard-672A3655: G***; kibuzzard-672A3655
kibuzzard-68340179: G***; kibuzzard-68340179
